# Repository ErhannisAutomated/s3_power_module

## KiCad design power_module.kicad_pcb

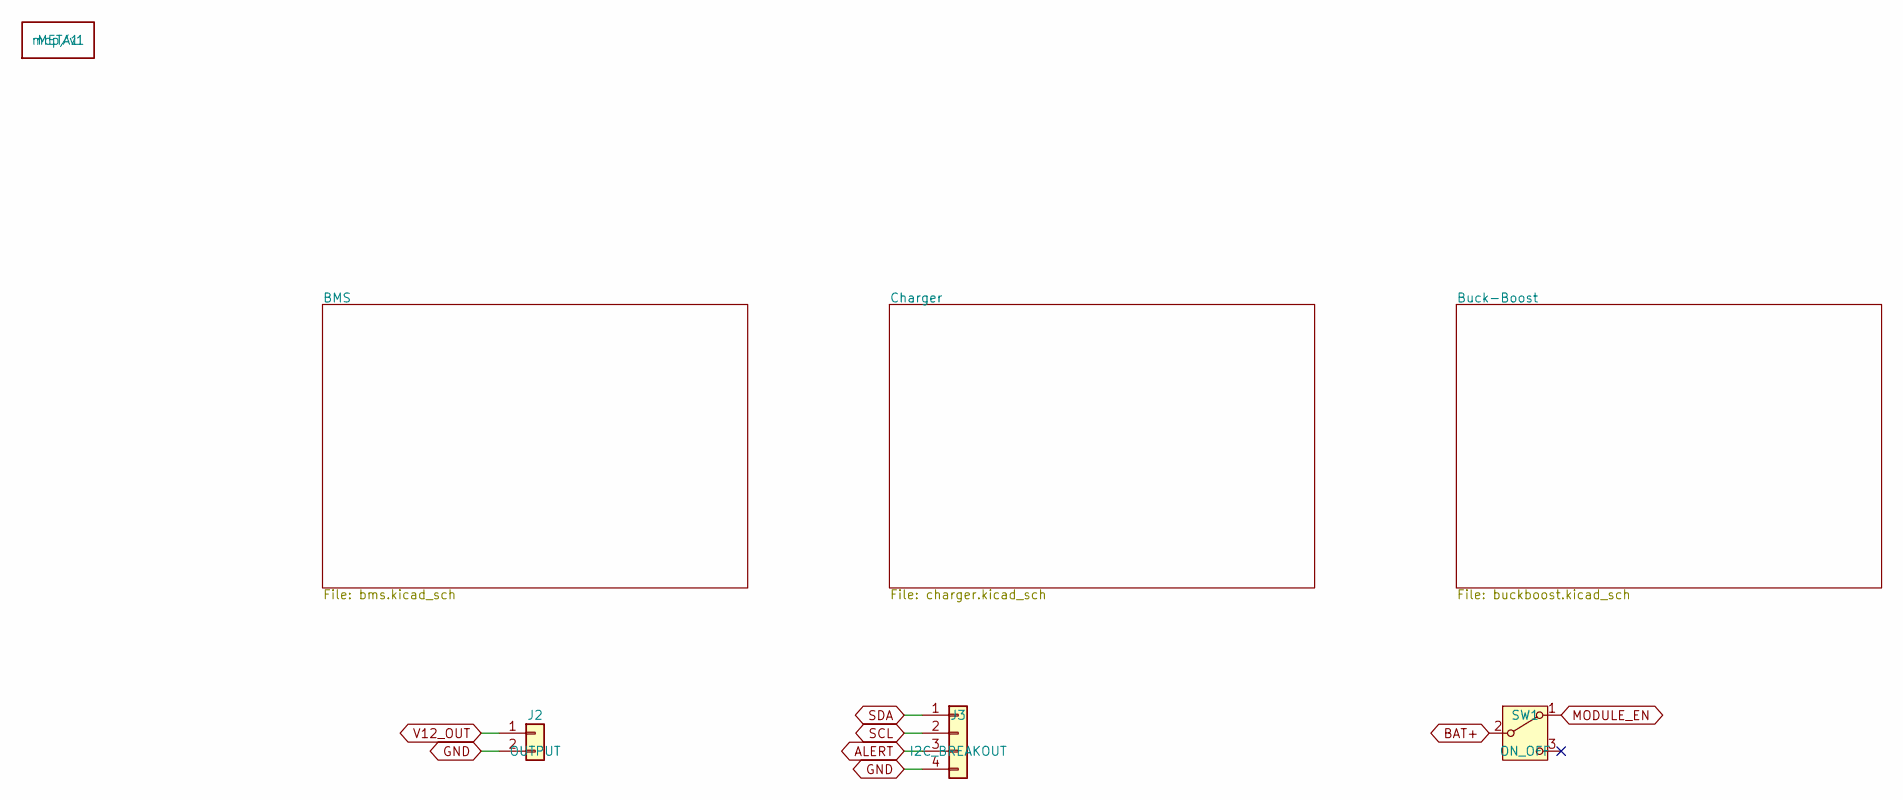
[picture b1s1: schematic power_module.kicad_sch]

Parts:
J2: OUTPUT; PinHeader_1x02_P2.54mm_Vertical
J3: I2C_BREAKOUT; PinHeader_1x04_P2.54mm_Vertical
META1: mcp/v1
SW1: ON_OFF; SW_SPDT_PCM12

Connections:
ALERT: J3.3; also elsewhere on the board
BAT+: SW1.2 (B); also elsewhere on the board
GND: J2.2, J3.4; also elsewhere on the board
MODULE_EN: SW1.1 (A); also elsewhere on the board
SCL: J3.2; also elsewhere on the board
SDA: J3.1; also elsewhere on the board
V12_OUT: J2.1; also elsewhere on the board

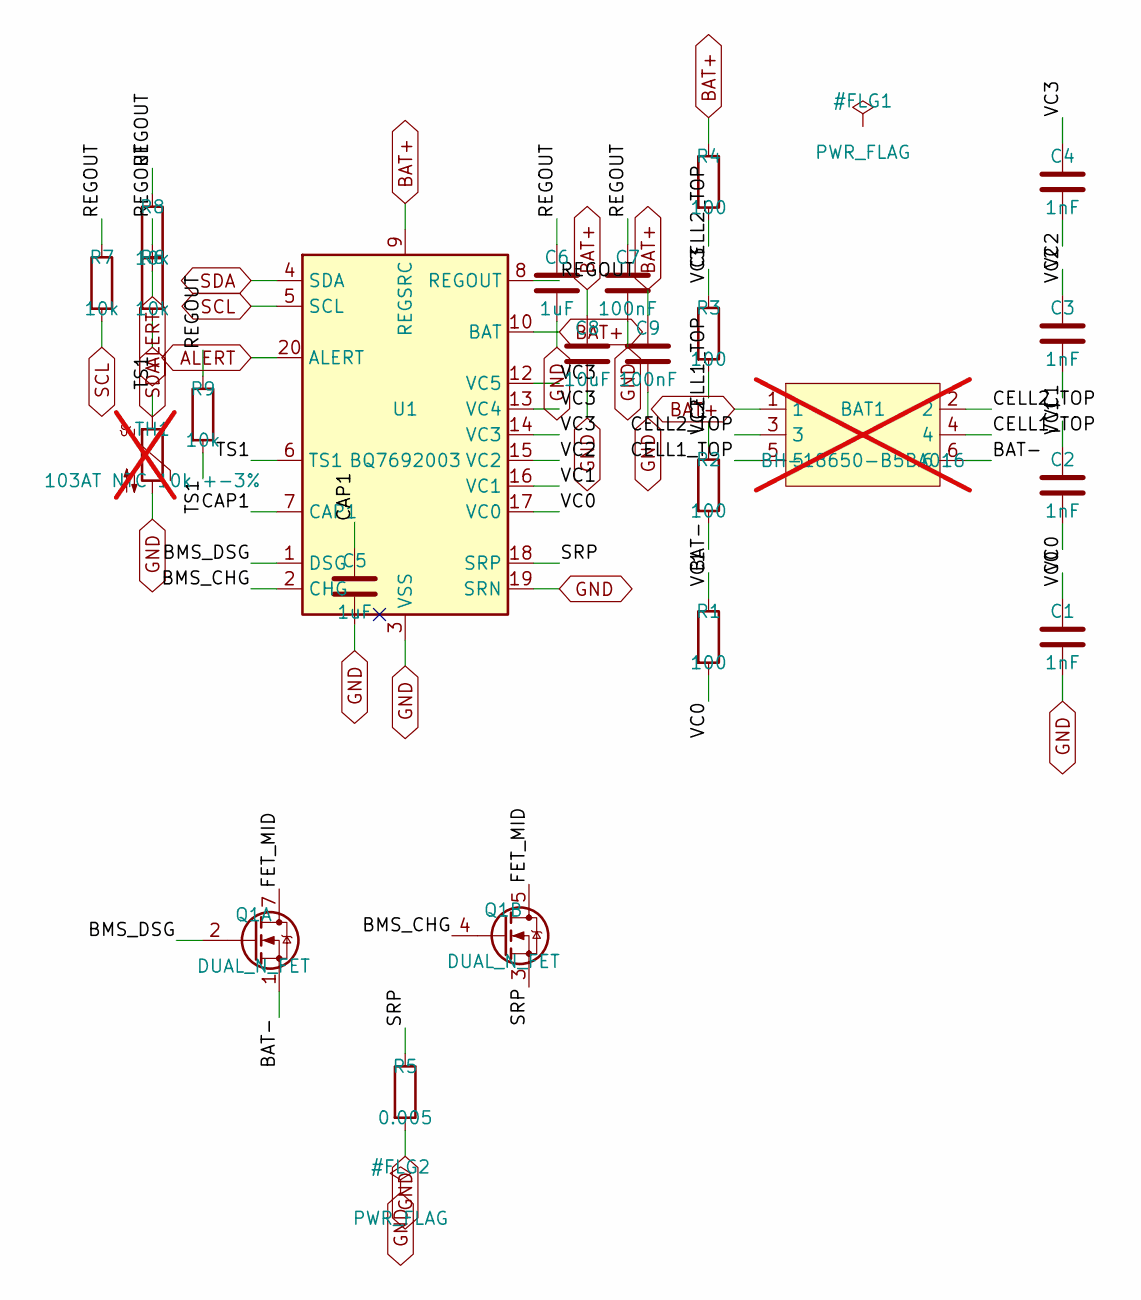
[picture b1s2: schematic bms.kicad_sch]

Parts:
BAT1: BH-18650-B5BA016; BAT-SMD_BH-18650-B5BA016; LCSC C19184086; not fitted
C1, C2, C3, C4: 1nF; C_0603_1608Metric; LCSC C1588
C5, C6: 1uF; C_0805_2012Metric; LCSC C28323
C7, C9: 100nF; C_0603_1608Metric; LCSC C14663
C8: 10uF; C_0805_2012Metric; LCSC C15850
Q1: DUAL_N_FET; SOIC-8_3.9x4.9mm_P1.27mm; LCSC C353066
R1, R2, R3, R4: 100; R_0603_1608Metric; LCSC C22775
R5: 0.005; R_1206_3216Metric; LCSC C2988648
R6, R7, R8, R9: 10k; R_0603_1608Metric; LCSC C25804
TH1: 103AT NTC 10k +-3%; R_Axial_DIN0204_L3.6mm_D1.6mm_P1.90mm_Vertical; not fitted
U1: BQ7692003; TSSOP-20_4.4x6.5mm_P0.65mm; LCSC C601650

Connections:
ALERT: R8.2, U1.20 (ALERT); also elsewhere on the board
BAT+: BAT1.1, C8.1, C9.1, R4.1, U1.9 (REGSRC), U1.10 (BAT); also elsewhere on the board
BAT-: BAT1.6, Q1.1 (S1), R1.1
BMS_CHG: Q1.4 (G2), U1.2 (CHG)
BMS_DSG: Q1.2 (G1), U1.1 (DSG)
CAP1: C5.1, U1.7 (CAP1)
CELL1_TOP: BAT1.4, BAT1.5, R2.1
CELL2_TOP: BAT1.2, BAT1.3, R3.1
FET_MID: Q1.5 (D2), Q1.6 (D2), Q1.7 (D1), Q1.8 (D1)
GND: C1.2, C5.2, C6.2, C7.2, C8.2, C9.2, R5.2, TH1.2, U1.3 (VSS), U1.19 (SRN); also elsewhere on the board
REGOUT: C6.1, C7.1, R6.1, R7.1, R8.1, R9.1, U1.8 (REGOUT)
SCL: R7.2, U1.5 (SCL); also elsewhere on the board
SDA: R6.2, U1.4 (SDA); also elsewhere on the board
SRP: Q1.3 (S2), R5.1, U1.18 (SRP)
TS1: R9.2, TH1.1, U1.6 (TS1)
VC0: C1.1, C2.2, R1.2, U1.17 (VC0)
VC1: C2.1, C3.2, R2.2, U1.16 (VC1)
VC2: C3.1, C4.2, R3.2, U1.15 (VC2)
VC3: C4.1, R4.2, U1.12 (VC5), U1.13 (VC4), U1.14 (VC3)

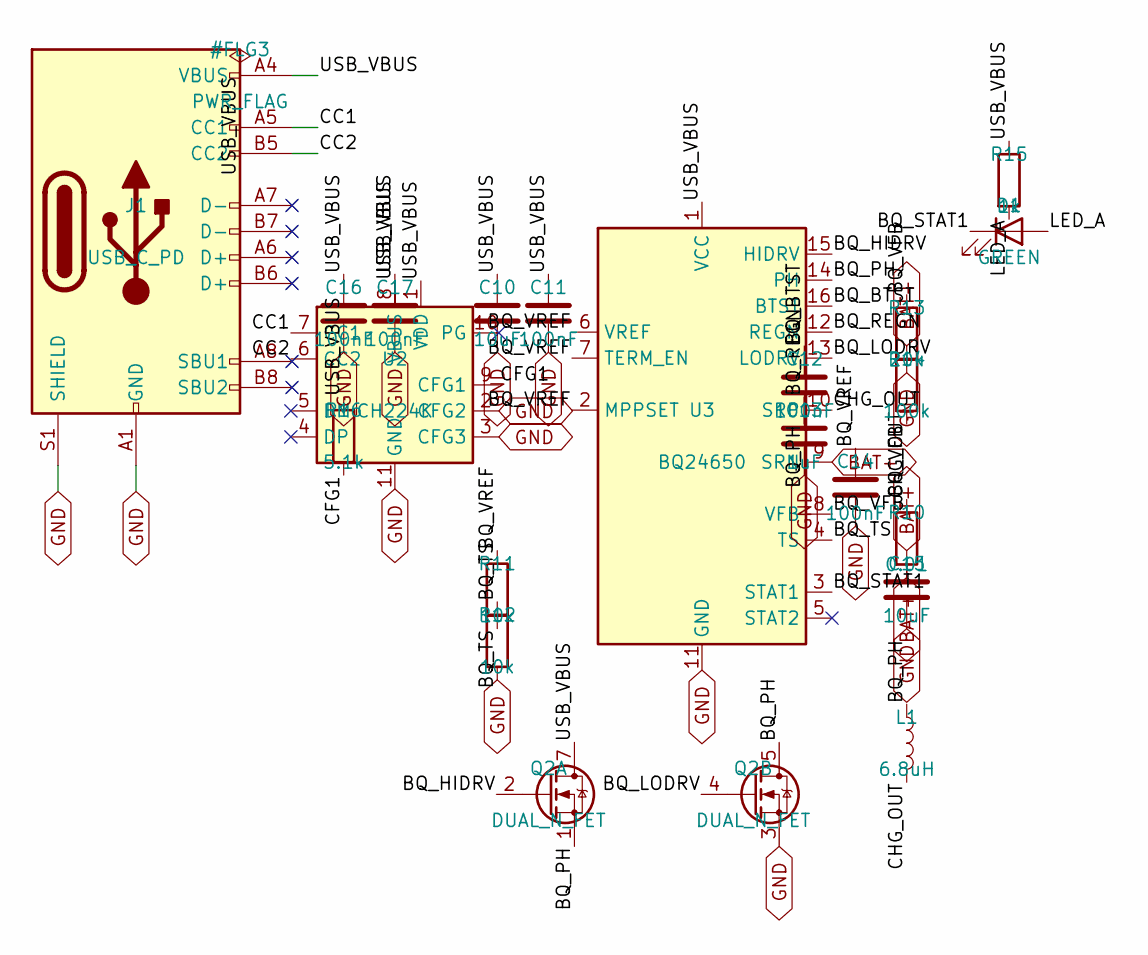
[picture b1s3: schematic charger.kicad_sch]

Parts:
C10, C15: 10uF; C_0805_2012Metric; LCSC C15850
C11, C12, C14, C16, C17: 100nF; C_0603_1608Metric; LCSC C14663
C13: 1uF; C_0805_2012Metric; LCSC C28323
D1: GREEN; LED_0805_2012Metric; LCSC C2297
J1: USB_C_PD; USB_C_Receptacle_HRO_TYPE-C-31-M-12; LCSC C165948
L1: 6.8uH; IND-SMD_L7.0-W6.6; LCSC C167221
Q2: DUAL_N_FET; SOIC-8_3.9x4.9mm_P1.27mm; LCSC C353066
R10: 0.01; R_1206_3216Metric; LCSC C601097
R11, R12: 10k; R_0603_1608Metric; LCSC C25804
R13: 20k; R_0603_1608Metric; LCSC C4184
R14: 100k; R_0603_1608Metric; LCSC C25803
R15: 1k; R_0603_1608Metric; LCSC C21190
R16: 5.1k; R_0603_1608Metric; LCSC C23186
U2: CH224K; MSOP-10_3x3mm_P0.5mm; LCSC C970725
U3: BQ24650; QFN-16-1EP_3x3mm_P0.5mm_EP1.7x1.7mm; LCSC C53712

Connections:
BAT+: C15.1, R10.2, R14.1, U3.9 (SRN); also elsewhere on the board
BQ_BTST: C12.1, U3.16 (BTST)
BQ_HIDRV: Q2.2 (G1), U3.15 (HIDRV)
BQ_LODRV: Q2.4 (G2), U3.13 (LODRV)
BQ_PH: C12.2, L1.1, Q2.1 (S1), Q2.5 (D2), Q2.6 (D2), U3.14 (PH)
BQ_REGN: C13.1, U3.12 (REGN)
BQ_STAT1: D1.1 (K), U3.3 (STAT1)
BQ_TS: R11.2, R12.1, U3.4 (TS)
BQ_VFB: R13.1, R14.2, U3.8 (VFB)
BQ_VREF: C14.1, R11.1, U3.2 (MPPSET), U3.6 (VREF), U3.7 (TERM_EN)
CC1: J1.A5 (CC1), U2.7 (CC1)
CC2: J1.A8 (SBU1), J1.B5 (CC2), U2.6 (CC2)
CFG1: R16.2, U2.9 (CFG1)
CHG_OUT: L1.2, R10.1, U3.10 (SRP)
GND: C10.2, C11.2, C13.2, C14.2, C15.2, C16.2, C17.2, J1.A1 (GND), J1.A12 (GND), J1.B1 (GND), J1.B12 (GND), J1.S1 (SHIELD), Q2.3 (S2), R12.2, R13.2, U2.2 (CFG2), U2.3 (CFG3), U2.11 (GND), U3.11 (GND), U3.17 (GND); also elsewhere on the board
LED_A: D1.2 (A), R15.2
USB_VBUS: C10.1, C11.1, C16.1, C17.1, J1.A4 (VBUS), J1.A9 (VBUS), J1.B4 (VBUS), J1.B9 (VBUS), Q2.7 (D1), Q2.8 (D1), R15.1, R16.1, U2.1 (VDD), U2.8 (VBUS), U3.1 (VCC)

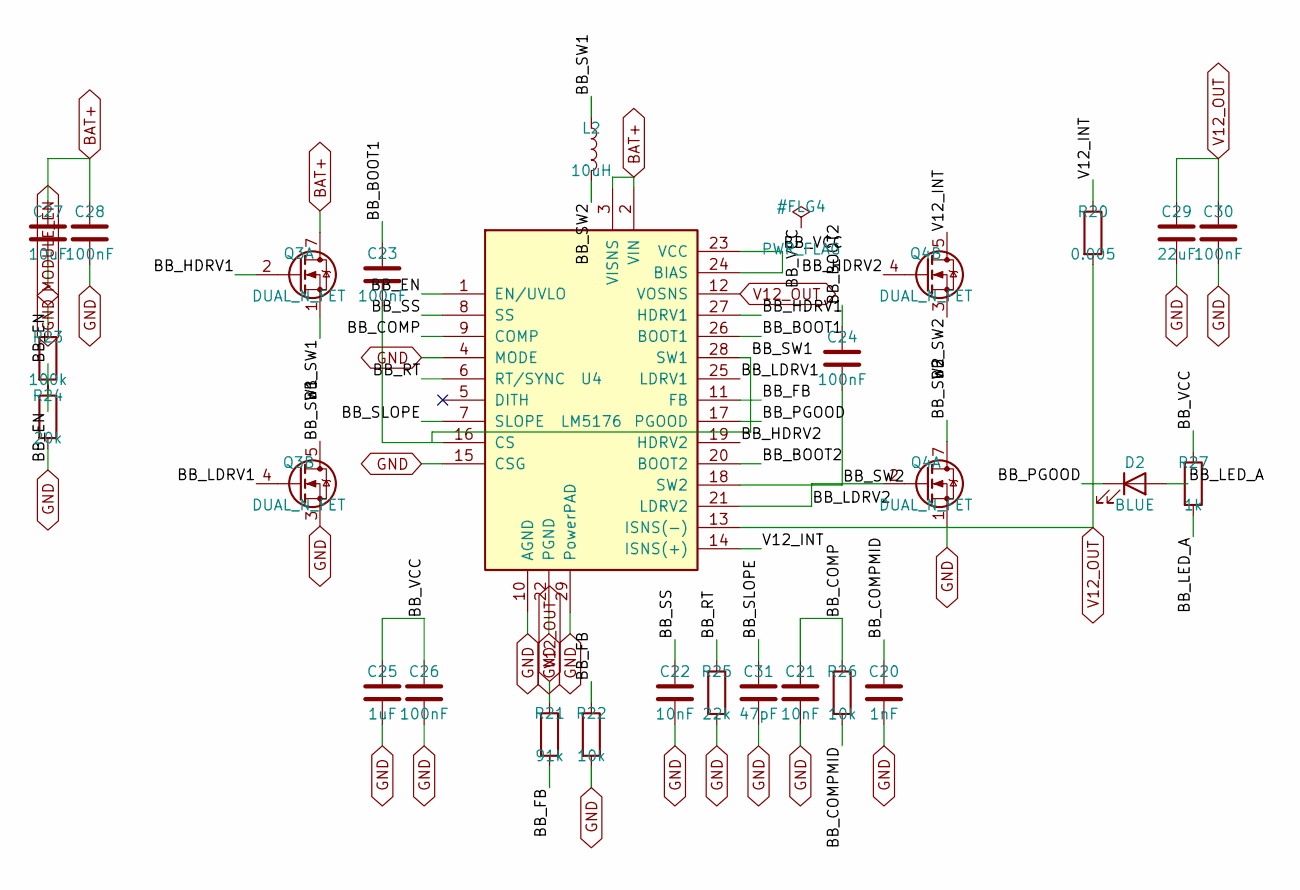
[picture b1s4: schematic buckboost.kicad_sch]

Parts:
C20: 1nF; C_0603_1608Metric; LCSC C1588
C21, C22: 10nF; C_0603_1608Metric; LCSC C57112
C23, C24, C26, C28, C30: 100nF; C_0603_1608Metric; LCSC C14663
C25: 1uF; C_0805_2012Metric; LCSC C28323
C27: 10uF; C_0805_2012Metric; LCSC C15850
C29: 22uF; C_1206_3216Metric; LCSC C12891
C31: 47pF; C_0603_1608Metric; LCSC C1671
D2: BLUE; LED_0805_2012Metric; LCSC C84259
L2: 10uH; IND-SMD_L7.1-W6.6; LCSC C41407100
Q3, Q4: DUAL_N_FET; SOIC-8_3.9x4.9mm_P1.27mm; LCSC C353066
R20: 0.005; R_1206_3216Metric; LCSC C2988648
R21: 91k; R_0603_1608Metric; LCSC C2907077
R22, R26: 10k; R_0603_1608Metric; LCSC C25804
R23: 100k; R_0603_1608Metric; LCSC C25803
R24: 20k; R_0603_1608Metric; LCSC C4184
R25: 22k; R_0603_1608Metric; LCSC C31850
R27: 1k; R_0603_1608Metric; LCSC C21190
U4: LM5176; HTSSOP-28-1EP_4.4x9.7mm_P0.65mm_EP2.85x5.4mm_ThermalVias; LCSC C442493

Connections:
BAT+: C27.1, C28.1, Q3.7 (D1), Q3.8 (D1), U4.2 (VIN), U4.3 (VISNS); also elsewhere on the board
BB_BOOT1: C23.1, U4.26 (BOOT1)
BB_BOOT2: C24.1, U4.20 (BOOT2)
BB_COMP: C21.1, R26.1, U4.9 (COMP)
BB_COMPMID: C20.1, R26.2
BB_EN: R23.2, R24.1, U4.1 (EN/UVLO)
BB_FB: R21.2, R22.1, U4.11 (FB)
BB_HDRV1: Q3.2 (G1), U4.27 (HDRV1)
BB_HDRV2: Q4.4 (G2), U4.19 (HDRV2)
BB_LDRV1: Q3.4 (G2), U4.25 (LDRV1)
BB_LDRV2: Q4.2 (G1), U4.21 (LDRV2)
BB_LED_A: D2.2 (A), R27.2
BB_PGOOD: D2.1 (K), U4.17 (PGOOD)
BB_RT: R25.1, U4.6 (RT/SYNC)
BB_SLOPE: C31.1, U4.7 (SLOPE)
BB_SS: C22.1, U4.8 (SS)
BB_SW2: C24.2, L2.2, Q4.3 (S2), Q4.7 (D1), Q4.8 (D1), U4.18 (SW2)
BB_VCC: C25.1, C26.1, R27.1, U4.23 (VCC), U4.24 (BIAS)
GND: C20.2, C21.2, C22.2, C25.2, C26.2, C27.2, C28.2, C29.2, C30.2, C31.2, Q3.3 (S2), Q4.1 (S1), R22.2, R24.2, R25.2, U4.4 (MODE), U4.10 (AGND), U4.15 (CSG), U4.22 (PGND), U4.29 (PowerPAD); also elsewhere on the board
MODULE_EN: R23.1; also elsewhere on the board
V12_INT: Q4.5 (D2), Q4.6 (D2), R20.1, U4.14 (ISNS(+))
V12_OUT: C29.1, C30.1, R20.2, R21.1, U4.12 (VOSNS), U4.13 (ISNS(-)); also elsewhere on the board

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
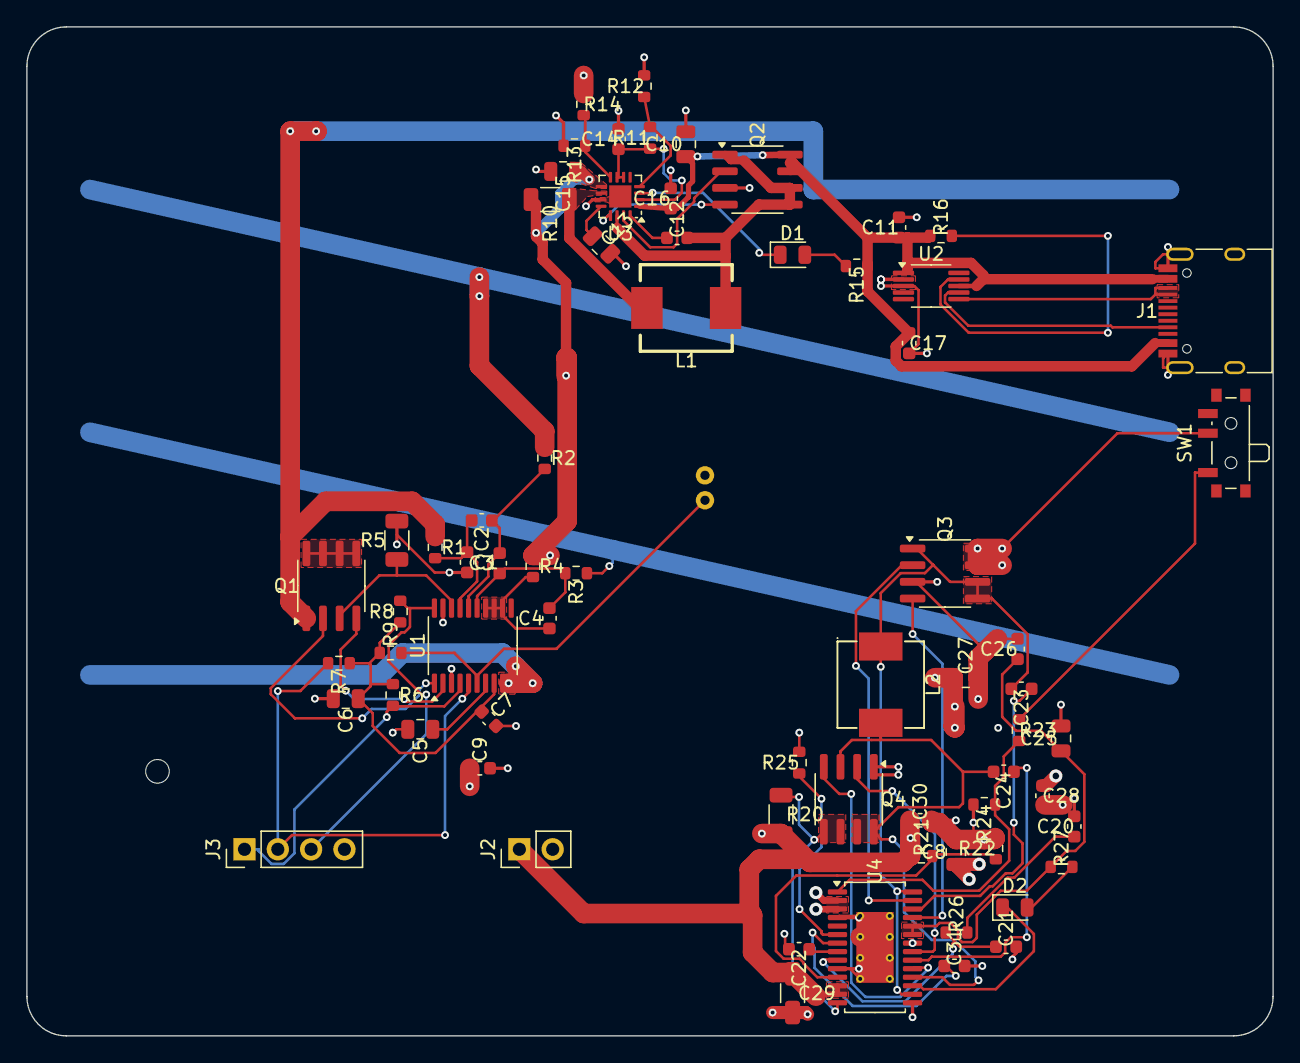
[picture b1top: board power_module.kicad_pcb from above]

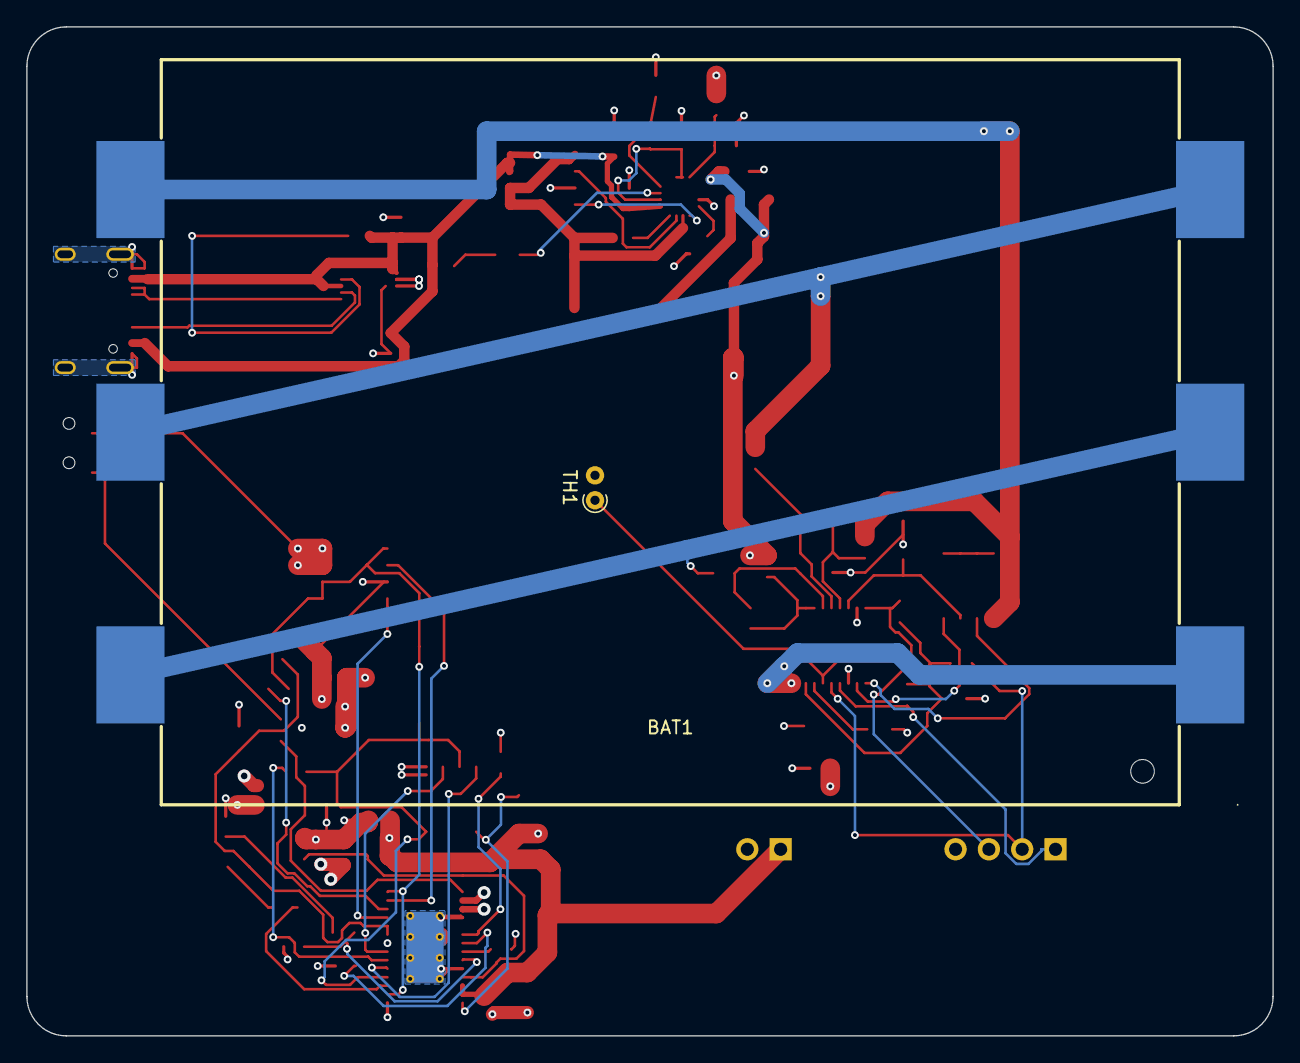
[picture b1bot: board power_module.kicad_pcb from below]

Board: 4 copper layers, 95.0 x 76.9 mm, 71 parts (2 on the bottom side), 55 nets.

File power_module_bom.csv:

value,footprint,quantity,references,LCSC,Description
BQ7692003,Package_SO:TSSOP-20_4.4x6.5mm_P0.65mm,1,U1,C601650,3S BMS controller
100,Resistor_SMD:R_0603_1608Metric,4,R1;R2;R3;R4,C22775,Cell-tap R to VC0
1nF,Capacitor_SMD:C_0603_1608Metric,5,C1;C2;C3;C4;C20,C1588,VC0 tap filter
DUAL_N_FET,Package_SO:SOIC-8_3.9x4.9mm_P1.27mm,4,Q1;Q3;Q4;Q2,C353066,Protection FETs (CHG/DSG)
0.005,Resistor_SMD:R_1206_3216Metric,2,R5;R20,C2988648,Cell current sense
1uF,Capacitor_SMD:C_0805_2012Metric,4,C5;C6;C25;C13,C28323,CAP1 bootstrap
100nF,Capacitor_SMD:C_0603_1608Metric,12,C7;C9;C23;C24;C28;C30;C26;C11;C12;C14;C16;C17,C14663,REGOUT bypass
10uF,Capacitor_SMD:C_0805_2012Metric,4,C8;C27;C10;C15,C15850,BAT/REGSRC bulk
10k,Resistor_SMD:R_0603_1608Metric,8,R6;R7;R8;R9;R22;R26;R11;R12,C25804,SDA pull-up
NTC_10k,Resistor_SMD:R_0603_1608Metric,1,TH1,C13564,Temperature sense NTC
BH-18650-B5BA016,power_module_lib:BAT-SMD_BH-18650-B5BA016,1,BAT1,C19184086,3S 18650 cell holder
LM5176,Package_SO:HTSSOP-28-1EP_4.4x9.7mm_P0.65mm_EP2.85x5.4mm_ThermalVias,1,U4,C442493,Buck-boost controller
10uH,power_module_lib:IND-SMD_L7.1-W6.6,1,L2,C41407100,Buck-boost inductor
100k,Resistor_SMD:R_0603_1608Metric,2,R23;R14,C25803,Soft-start R
20k,Resistor_SMD:R_0603_1608Metric,2,R24;R13,C4184,EN divider
22uF,Capacitor_SMD:C_1206_3216Metric,1,C29,C12891,VOUT bulk
BLUE,LED_SMD:LED_0805_2012Metric,1,D2,C84259,Output status LED
1k,Resistor_SMD:R_0603_1608Metric,2,R27;R15,C21190,D2 current limit
91k,Resistor_SMD:R_0603_1608Metric,1,R21,C2907077,FB top (12V out)
10nF,Capacitor_SMD:C_0603_1608Metric,2,C22;C21,C57112,Loop comp 1
22k,Resistor_SMD:R_0603_1608Metric,1,R25,C31850,Loop comp R
47pF,Capacitor_SMD:C_0603_1608Metric,1,C31,C1671,Loop comp ff
CH224K,Package_SO:MSOP-10_3x3mm_P0.5mm,1,U2,C970725,USB-PD trigger 12V
BQ24650,Package_DFN_QFN:QFN-16-1EP_3x3mm_P0.5mm_EP1.7x1.7mm,1,U3,C53712,Sync buck charger controller
6.8uH,power_module_lib:IND-SMD_L7.0-W6.6,1,L1,C167221,Charger output inductor
0.01,Resistor_SMD:R_1206_3216Metric,1,R10,C601097,Charger current sense
GREEN,LED_SMD:LED_0805_2012Metric,1,D1,C2297,Charge status LED
5.1k,Resistor_SMD:R_0603_1608Metric,1,R16,C23186,USB-C CC pull-down
USB_C_PD,Connector_USB:USB_C_Receptacle_HRO_TYPE-C-31-M-12,1,J1,C165948,USB-C input (PD-capable)
OUTPUT,Connector_PinHeader_2.54mm:PinHeader_1x02_P2.54mm_Vertical,1,J2,,
I2C_BREAKOUT,Connector_PinHeader_2.54mm:PinHeader_1x04_P2.54mm_Vertical,1,J3,,
ON_OFF,Button_Switch_SMD:SW_SPDT_PCM12,1,SW1,,

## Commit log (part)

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2026-05-13 pcb: first-pass placement for all 71 footprints
    Layout floorplan: 95x110 mm rounded rectangle. Cell holder (BAT1)
    across the top half centered at (47.5, 23). Bottom half partitioned
    into three column strips:
    - x = 0-30: BMS (U1, R1-9, C1-9, Q1, R5, TH1).
    - x = 30-60: charger (J1 region, U2, U3, Q2, L1, R10-16, D1, C10-17).
    - x = 60-95: buck-boost (U4, Q3-Q4, L2, D2, R20-27, C20-31).
2026-05-13 pcb: persist all 71 placement moves via direct file rewrite
    Workaround for the MCP server bug recorded in mcp_server_issues.md
    (commit b8183d8 in KiCAD-MCP-Server develop): move_component
    silently operated on a different in-memory BOARD than save_project
    wrote, so the first save in this layout pass landed the auto-import
    grid coords instead of the placement.
    Recovered the intended positions from get_component_list (which
2026-05-13 pcb: rewrite (at) positions with corrected helper script
    apply_positions.py had an off-by-N bug: it advanced its byte cursor
    using the *post-substitution* block length rather than the original
    slice end, so any (at X Y rot) replacement that wrote fewer bytes
    than the source line left the cursor lagging. The next iteration
    then re-emitted the tail bytes of the previous footprint, injecting
    stray top-level ')' characters into the file (which manifested as
2026-05-13 pcb: add GND (In1.Cu, B.Cu) and BAT+ (In2.Cu) copper pours
    4-layer stackup is now:
    L1 F.Cu — signal routing
    L2 In1.Cu — GND fill
    L3 In2.Cu — BAT+ fill (highest-current rail)
    L4 B.Cu — GND fill + signal routing
2026-05-13 pcb: iterate 1 — clean tracks, drop B.Cu pour, spread tap-row + R/Cs
    Iteration to reduce the unrouted count from freerouting v1 (66/184).
    Changes this pass:
    - Stripped 412 tracks + 74 vias from previous SES import for a
    clean re-route from the DSN.
    - Removed B.Cu GND copper pour (was occluding signal routing on
    L4; In1.Cu still has GND fill which is the planar return).
2026-05-13 pcb: autoroute v2 with B.Cu freed up — 379 tracks, 79 vias
    Slightly worse than v1 (412/74). Suggests the iteration changes
    (removed B.Cu GND, spread tap row, moved U2) didn't help the
    freerouting heuristic. 34 via_dangling errors in DRC indicate
    incomplete routing attempts.
    Also save: BOM csv export attempt (currently captures only the 3
    top-level parts because export_bom doesn't walk hierarchical sheets;
2026-05-13 notes: 2026-05-13 PCB layout + autoroute session resume guide
2026-05-13 pcb: export BOM (32 lines, hierarchical fix loaded), gerber, pos
    BOM: 32 unique value+footprint lines covering 71 components; LCSC
    and Description columns populated (export_bom hierarchical-walk fix
    loaded after MCP restart).
    Gerber: 25 layer files + 2 drill (PTH/NPTH) + job file in gerber/.
    Includes both inner copper layers (g1=GND, g2=BAT+ planned but no
    pour landed — see notes).
2026-05-13 pcb: re-route v3 with In2.Cu BAT+ pour — major BAT+ improvement
    After the MCP add_layer fix and the In2.Cu BAT+ pour was added, ripped
    up all tracks/vias and ran a fresh 25-pass freerouting.
    Per-net comparison (v2 -> v3) on the big power nets:
    BAT+: F.Cu 218.5mm / 38 segs / 0 vias -> F.Cu 15.9mm / 10 segs / 9 vias
    GND: already-pour-routed -> F.Cu 39.7mm / 53 segs / 34 vias
    BAT+ is now mostly carried on the In2.Cu BAT+ pour with short F.Cu stubs
2026-05-13 notes: 2026-05-14 BAT+ inner pour + re-route session resume guide
    Documents the add_layer fix, the In2.Cu pour repair, and the v3
    re-route results. Two cold-resume paths laid out (close routing
    gap vs. move on to a new design).
2026-05-14 pcb: fix stale pad rotations on all 57 rotated footprints
    Background: yesterday's `apply_positions.py` recovered footprint
    positions after the place_component dispatch bug. It directly
    rewrote the `(at X Y rot)` line on each footprint via regex, but
    did NOT touch the per-pad local rotation fields.
    KiCad's renderer + pcbnew API combine footprint_rot for the pad's
    WORLD POSITION (centre coordinate) but use only the pad's LOCAL
2026-05-14 pcb: J1 inward, J2/J3 horizontal, BAT1 to back + DNP
    User feedback after the pad-rotation fix:
    - J1 was rotated -90° with pins facing the right (board edge) so the
    USB-C receptacle opening faced inward; correct orientation is
    +90° (pins inward, opening to edge). Net rotation change: +180°.
    - J2 and J3 are 1x02 / 1x04 pin headers placed at y=103 mm on a
    110 mm tall board. Vertical-pin-row footprints meant the pin
2026-05-14 pcb: re-route v6 — C24 nudged out of L2 footprint; zero shorts
    Yesterday's apply_positions.py placed C24 (0603 bootstrap cap) at
    (62, 80), which falls inside L2's footprint bbox (61-69, 76.6-83.4
    mm). v4's three shorting_items DRC errors all originated here.
    Moved C24 to (58.5, 80) — into the 5 mm clear gap between C15
    (right edge 56.01) and L2 (left edge 61.02). ~3.5 mm extra trace
    length to the BB_BOOT2 / BB_SW2 nets is acceptable for a 100 nF
2026-05-14 notes: 2026-05-14 afternoon session — pad rotation + v6 re-route
    Documents the pad-rotation root cause (user's visual catch), the
    57-footprint repair, the J1/J2/J3 + BAT1 layout corrections, and
    the v6 routing result (616 tracks, 0 shorts). Plus the MCP
    `self.board` cache gotcha that bit us during the C24 nudge.
2026-05-16 pcb: close 3 of 4 cap unconnects (C28 BAT+, C7 REGOUT, C11 USB_VBUS)
    C28.1 BAT+: route_pad_to_pad to C27.1 on F.Cu, width 0.4 mm (1.5 mm
    shorted to C15.2 GND at 1.43 mm clearance).
    C7.1 REGOUT: 3-segment waypoint around U1's east edge — east to
    X=16.85 (avoids GND via at 16.29 with 0.16 mm clearance), south, west
    into C7.1.
    C11.1 USB_VBUS: 3-segment waypoint around C11.2 GND south — direct
2026-05-16 pcb: close U4.2/U4.3 BAT+ trunk unconnect
    2-segment waypointed route U4.3 (75.075, 82.86) → south at X=75.075 →
    east at Y=86.24 into C28.1, F.Cu width 0.4 mm. Direct line was
    blocked by C28.2 GND pad — caught by the new route_trace
    checkObstacles default-on check (KiCAD-MCP-Server c4fe565). Two
    write-attempts total, no DRC surprises.
    NOTES updated to reflect 5 remaining unconnects (down from 6) and
2026-05-16 notes: 2026-05-18 session — tooling sprint summary
    Six MCP commits, plus C26/J1.A9 v2 live test results, plus the
    dedupe_traces application that just dropped 332 duplicates from
    the PCB.
2026-05-16 pcb: clean placement restart — all 71 footprints repositioned by functional group
    Strip-and-re-place pass per the agreed restart plan in NOTES.md.
    Anchors first (BAT1 cell holder B.Cu, J1 USB-C right edge,
    J2/J3/SW1 bottom edge), then major ICs (U1 BMS, U2 PD, U3 charger,
    U4 buck-boost) + power FETs + inductors. Decoupling/bypass caps
    placed via place_near against their actual electrical targets
    (verified by pad-net lookup after one mis-assignment — C2 was
2026-05-19 Moved footprints around a little
2026-05-19 pcb: post-user spread pass — relieve crowding around U1 and U4
    User adjustment pass moved BAT1 up and components into a compact
    lower band; cluster-density check showed 17 components within 8mm
    of U1 (BMS) and 17 within 8mm of U4 (buck-boost), too tight to route.
    This pass:
    - Shifts U4 +6mm right (84,88) for thermal/edge clearance from
    BAT1 cell holder B.Cu pads (user-suggested in case the integrity-
2026-05-19 Ehh, remove accidental ephemeral files
2026-05-19 Inspecting progress
2026-05-19 pcb: north-spread BMS + charger into upper-half BAT1 envelope
    Moved U1 BMS + Q1 + R5 sense + 17 satellites to NW quadrant (y=33-45),
    moved U3 charger + L1 + R10 + Q2 + 9 satellites to NE quadrant
    (y=35-45). Buck-boost U4 cluster stays south, output stage stays south.
    The upper-half F.Cu was empty since BAT1 lives on B.Cu — used that
    real estate to relieve density.
    analyze_congestion result:
2026-05-19 Resized board and moved pieces back onto BAT1 area
2026-05-19 notes: 2026-05-19 session — placement tooling sprint summary
    Records the session's tooling shipped (analyze_congestion,
    get_ratsnest, relax_placement v1, auto-save fix), the board
    state after the relax pass (improved metrics but per user
    assessment U4/U1 areas still not routable), the 2026-05-20
    plan (unify schematic + PCB autoplacers per task #186), and
    the routing-tool gaps observed (route_trace clearance check,
2026-05-19 Testing pcb autoplacer first pass
2026-05-20 more changes
2026-05-26 Locked U4
2026-05-26 notes: 2026-05-26 — autoroute post-mortem (4 root causes diagnosed)
2026-05-26 re-route attempt: DSN plane fix verified; pre-route on B.Cu
    Three-pass re-route exercising yesterday's MCP fixes. Net change:
    Attempt #1 (clean autoroute):
    - planeLayersFlippedToPower: [In1.Cu, In2.Cu] confirmed the #203 fix
    is active. BAT+/BAT- now on F.Cu, not inner planes.
    - Trade-off discovered: with inner layers locked, freerouting
    couldn't bridge the 82mm cell-holder span and left CELL1_TOP,
2026-05-26 Moved U4 to bottom, away from pads and away from cells. Swapped SMD thermistor for THT and moved to B.Cu. Locked thermistor and BAT1.
2026-05-26 re-route with new U4 position: 0 shorts, 0 clearance
    After U4 moved south (extending the board), re-ran the routing
    pipeline: relax_placement → pre-route BAT1 trunks on B.Cu →
    autoroute. Best result of the day at this checkpoint.
    DRC: 65 errors / 106 warnings.
    - 0 shorts (the BAT1.2-in-U4-territory recurring issue is gone).
    - 0 clearance violations.
2026-05-26 apply via_orphan_pads + widen_return_paths: -15 DRC errors
    via_orphan_pads added vias adjacent to:
    - 26 orphan F.Cu GND pads (skipped 30 already connected, 6 no
    clearance). Notable: 3 vias on U4 pin 29 (LM5176 thermal pad).
    - 2 orphan F.Cu BAT+ pads (C9.1, C8.1).
    widen_return_paths widened 25 segments to 1.5 mm (POWER_4A width)
    across 23 high-current components. 37 segments blocked by clearance
2026-05-26 notes: via_orphan_pads + widen_return_paths shipped, -15 DRC errors
2026-05-26 apply via_orphan_pads v3 + widen_return_paths: 65 -> 38 DRC errors
    Re-applied the routing-finisher pipeline from the 574172e baseline
    with the v2 + v3 toolchain:
    via_orphan_pads v3 (orphan-chain detection + PTH/thermal-via skip
    + netclass-aware stub widths + stub-trace clearance check):
    - GND: 35 vias placed (skipped 4 already connected,
    8 no clearance — stub or via).
2026-05-26 notes: via_orphan_pads v3 + pin_zone_same_net + bonus fixes; board 65->38
2026-05-26 notes: pin_zone_same_net v2 (absMaxDist) + v3 (foreign-pad overlap) applied
2026-05-27 Working on fixing unconnects etc
2026-05-28 charger: incremental autoroute of 6/8 BQ signal nets
    First use of the new incremental autoroute (MCP #242): routed
    BQ_PH/BQ_VREF/BQ_VFB/BQ_BTST/BQ_LODRV/CHG_OUT (+69 tracks, +5 vias),
    leaving all non-charger copper byte-identical. refill_zones run after.
    Hand-off state for review: BQ_HIDRV and BQ_STAT1 still open, and ~8
    clashes remain where the freshly-routed charger tracks meet the existing
    USB_VBUS pour / fixed pads (the incremental-route caveat — freerouting
2026-05-28 Claude did some re-placing
